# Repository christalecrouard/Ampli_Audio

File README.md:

# Ampli_Audio
Projet d'amplificateur audio réalisé par les élèves de 3IMACS D

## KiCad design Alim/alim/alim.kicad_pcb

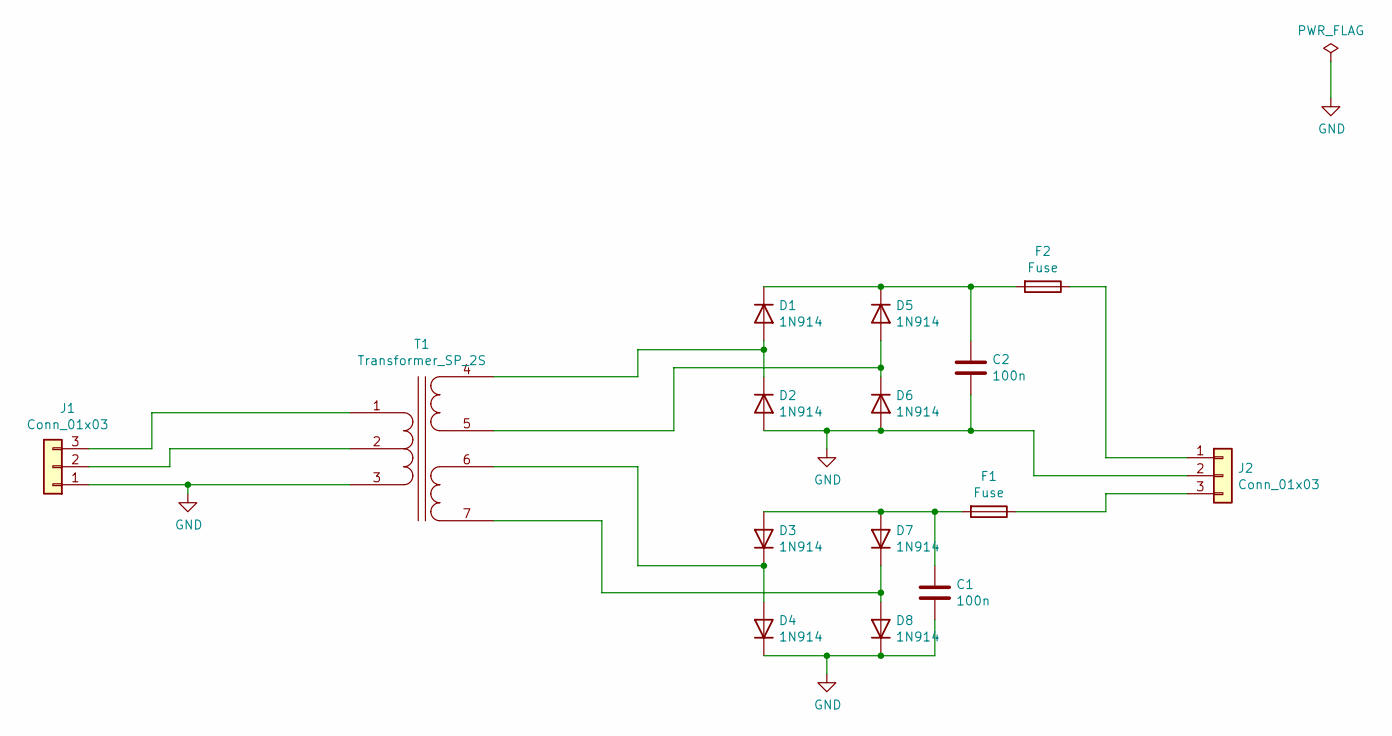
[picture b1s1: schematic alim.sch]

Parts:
C1, C2: 100n; C_Axial_L3.8mm_D2.6mm_P7.50mm_Horizontal
D1, D2, D3, D4, D5, D6, D7, D8: 1N914; D_DO-34_SOD68_P10.16mm_Horizontal
F1, F2: Fuse; Fuseholder_Cylinder-5x20mm_Bulgin_FX0457_Horizontal_Closed
J1, J2: Conn_01x03; FanPinHeader_1x03_P2.54mm_Vertical
T1: Transformer_SP_2S; Transformer_NF_ETAL_P2781_HandSoldering

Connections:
GND: C1.2, C2.2, D2.1 (A), D4.2 (K), D6.1 (A), D8.2 (K), J1.1, J2.2, T1.3 (IN-)
unnamed: C1.1, D3.1 (A), D7.1 (A), F1.2
unnamed: C2.1, D1.2 (K), D5.2 (K), F2.2
unnamed: D1.1 (A), D2.2 (K), T1.4 (OUT1A)
unnamed: D3.2 (K), D4.1 (A), T1.6 (OUT2A)
unnamed: D5.1 (A), D6.2 (K), T1.5 (OUT1B)
unnamed: D7.2 (K), D8.1 (A), T1.7 (OUT2B)
unnamed: F1.1, J2.3
unnamed: F2.1, J2.1
unnamed: J1.2, T1.2 (PM)
unnamed: J1.3, T1.1 (IN+)

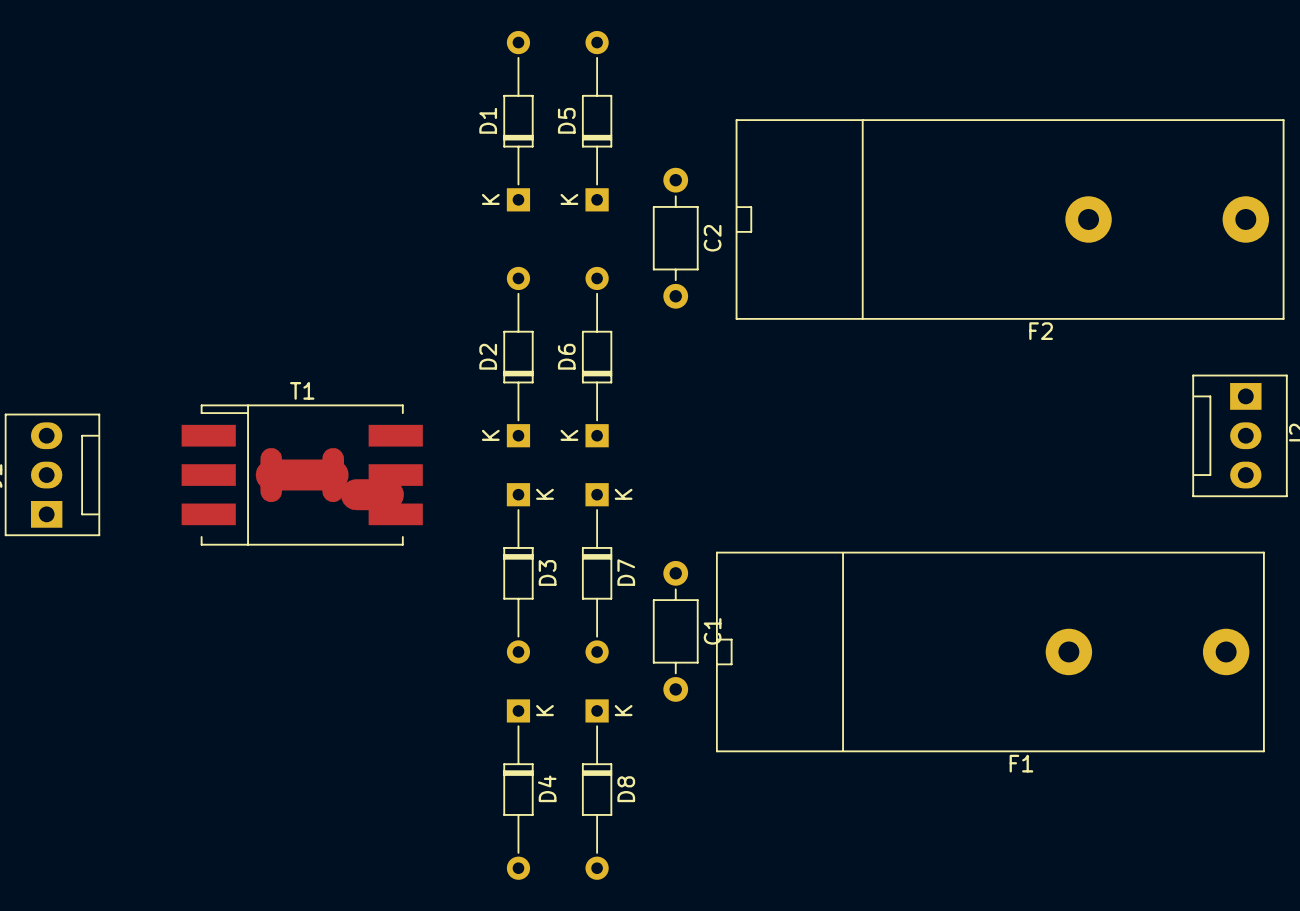
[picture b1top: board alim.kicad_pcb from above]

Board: 2 copper layers, 15 parts (0 on the bottom side), 11 nets.

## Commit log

2021-04-29 Alimentation
    Simulations + Schéma
2021-04-29 Mise en place du git
2021-04-29 Rename alim.asc to alim_simu_ltspice.asc
2021-04-29 UI Draw
